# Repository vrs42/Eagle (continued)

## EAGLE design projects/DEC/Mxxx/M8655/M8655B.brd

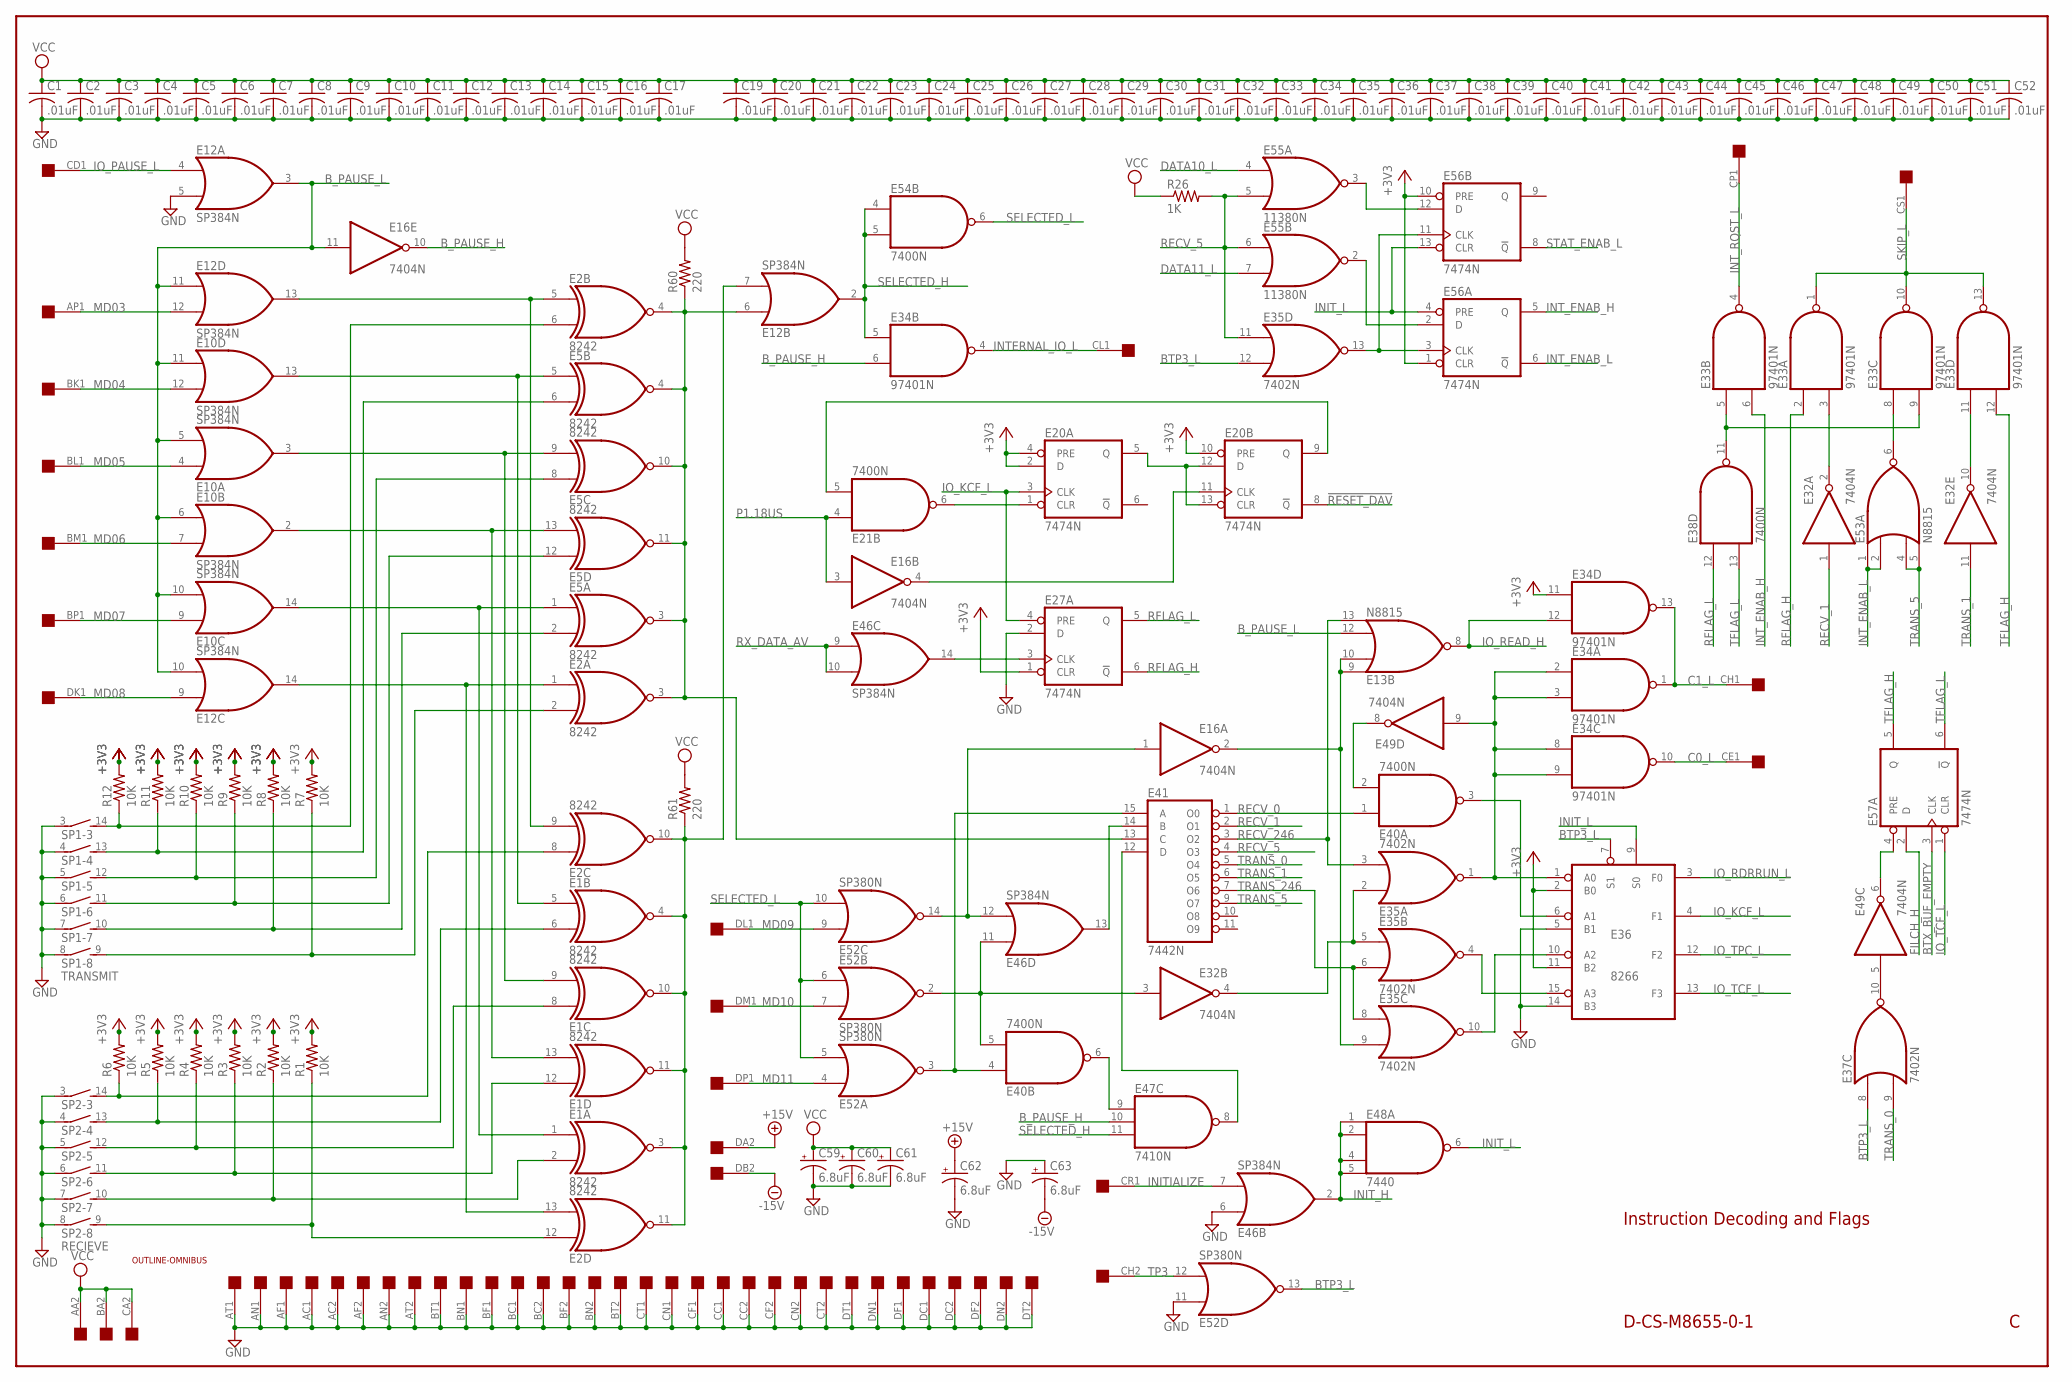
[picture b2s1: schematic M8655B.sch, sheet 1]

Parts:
C1, C2, C3, C4, C5, C6, C7, C8, C9, C10, C11, C12, C13, C14, C15, C16, C17, C19, C20, C21, C22, C23, C24, C25, C26, C27, C28, C29, C30, C31, C32, C33, C34, C35, C36, C37, C38, C39, C40, C41, C42, C43, C44, C45, C46, C47, C48, C49, C50, C51, C52: .01uF; C050-025X075
C59, C60, C61, C62, C63: 6.8uF; E12-8
E1, E2, E5: 8242; DIL14
E10, E12, E46: SP384N; DIL14
E13, E53: N8815; DIL14
E16, E32, E49: 7404N; DIL14
E20, E27, E56, E57: 7474N; DIL14
E21, E38, E40, E54: 7400N; DIL14
E33, E34: 97401N; DIL14
E35, E37: 7402N; DIL14
E36: 8266; DIL16
E41: 7442N; DIL16
E47: 7410N; DIL14
E48: 7440; DIL14
E52: SP380N; DIL14
E55: 11380N; DIL14
R1, R2, R3, R4, R5, R6, R7, R8, R9, R10, R11, R12: 10K; 0207/10
R26: 1K; 0207/10
R60, R61: 220; 0207/10
SP1: TRANSMIT; DIP08S
SP2: RECIEVE; DIP08S
U$1: OUTLINE-OMNIBUS; OMNIBUS
U$2: QUAD; EDGE-CON8

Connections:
!RESET_DAV: E20.8 (!Q); also elsewhere on the board
+3V3: E20.2 (D), E20.4 (PRE), E20.10 (PRE), E27.1 (CLR), E34.11 (I0), E36.2 (B0), E36.11 (B2), E56.1 (CLR), E56.10 (PRE), R1.2, R2.2, R3.2, R4.2, R5.2, R6.2, R7.2, R8.2, R9.2, R10.2, R11.2, R12.2; also elsewhere on the board
+15V: C62.+, U$2.DA2; also elsewhere on the board
-15V: C63.-, U$2.DB2; also elsewhere on the board
BTP3_L: E35.12 (I1), E36.7 (S1), E37.8 (I0), E52.13 (O)
BTX_BUF_EMPTY: E57.3 (CLK); also elsewhere on the board
B_PAUSE_H: E16.10 (O), E34.6 (I1), E47.10 (I1)
B_PAUSE_L: E10.5 (I1), E10.6 (I0), E10.10 (I1), E10.11 (I0), E12.3 (O), E12.10 (I1), E12.11 (I0), E13.12 (I2), E16.11 (I); also elsewhere on the board
C0_L: E34.10 (O), U$2.CE1
C1_L: E34.1 (O), E34.13 (O), U$2.CH1
DATA10_L: E55.4 (I0); also elsewhere on the board
DATA11_L: E55.7 (I1); also elsewhere on the board
FILCH_H: E57.2 (D); also elsewhere on the board
GND: C1.2, C2.2, C3.2, C4.2, C5.2, C6.2, C7.2, C8.2, C9.2, C10.2, C11.2, C12.2, C13.2, C14.2, C15.2, C16.2, C17.2, C19.2, C20.2, C21.2, C22.2, C23.2, C24.2, C25.2, C26.2, C27.2, C28.2, C29.2, C30.2, C31.2, C32.2, C33.2, C34.2, C35.2, C36.2, C37.2, C38.2, C39.2, C40.2, C41.2, C42.2, C43.2, C44.2, C45.2, C46.2, C47.2, C48.2, C49.2, C50.2, C51.2, C52.2, C59.-, C60.-, C61.-, C62.-, C63.+, E1.7 (GND), E2.7 (GND), E5.7 (GND), E10.1 (GND), E12.1 (GND), E12.5 (I1), E13.7 (GND), E16.7 (GND), E20.7 (GND), E21.7 (GND), E27.2 (D), E27.7 (GND), E32.7 (GND), E33.7 (GND), E34.7 (GND), E35.7 (GND), E36.5 (B1), E36.8 (GND), E36.14 (B3), E37.7 (GND), E38.7 (GND), E40.7 (GND), E41.8 (GND), E46.1 (GND), E46.6 (I0), E47.7 (GND), E48.7 (GND), E49.7 (GND), E52.1 (GND), E52.11 (I0), E53.7 (GND), E54.7 (GND), E55.1 (GND), E56.7 (GND), E57.7 (GND), SP1.3 (1), SP1.4 (1), SP1.5 (1), SP1.6 (1), SP1.7 (1), SP1.8 (1), SP2.3 (1), SP2.4 (1), SP2.5 (1), SP2.6 (1), SP2.7 (1), SP2.8 (1), U$2.AC1, U$2.AC2, U$2.AF1, U$2.AF2, U$2.AN1, U$2.AN2, U$2.AT1, U$2.AT2, U$2.BC1, U$2.BC2, U$2.BF1, U$2.BF2, U$2.BN1, U$2.BN2, U$2.BT1, U$2.BT2, U$2.CC1, U$2.CC2, U$2.CF1, U$2.CF2, U$2.CN1, U$2.CN2, U$2.CT1, U$2.CT2, U$2.DC1, U$2.DC2, U$2.DF1, U$2.DF2, U$2.DN1, U$2.DN2, U$2.DT1, U$2.DT2; also elsewhere on the board
INITIALIZE: E46.7 (I1), U$2.CR1
INIT_H: E46.2 (O), E48.1 (I0), E48.2 (I1), E48.4 (I2), E48.5 (I3); also elsewhere on the board
INIT_L: E36.9 (S0), E48.6 (O), E56.4 (PRE), E56.13 (CLR); also elsewhere on the board
INTERNAL_IO_L: E34.4 (O), U$2.CL1
INT_ENAB_H: E33.6 (I1), E56.5 (Q)
INT_ENAB_L: E53.1 (I0), E53.2 (I1), E56.6 (!Q)
INT_RQST_L: E33.4 (O), U$2.CP1
IO_KCF_L: E20.3 (CLK), E27.4 (PRE), E36.4 (F1)
IO_PAUSE_L: E12.4 (I0), U$2.CD1
IO_RDRRUN_L: E36.3 (F0); also elsewhere on the board
IO_READ_H: E13.8 (O), E34.12 (I1); also elsewhere on the board
IO_TCF_L: E36.13 (F3), E57.1 (CLR)
IO_TPC_L: E36.12 (F2); also elsewhere on the board
MD03: E12.12 (I1), U$2.AP1
MD04: E10.12 (I1), U$2.BK1
MD05: E10.4 (I0), U$2.BL1
MD06: E10.7 (I1), U$2.BM1
MD07: E10.9 (I0), U$2.BP1
MD08: E12.9 (I0), U$2.DK1
MD09: E52.9 (I0), U$2.DL1
MD10: E52.7 (I1), U$2.DM1
MD11: E52.4 (I0), U$2.DP1
unnamed: E2.6 (I1), R12.1, SP1.14 (2)
unnamed: E5.6 (I1), R11.1, SP1.13 (2)
unnamed: E5.8 (I0), R10.1, SP1.12 (2)
unnamed: E5.12 (I0), R9.1, SP1.11 (2)
unnamed: E5.2 (I1), R8.1, SP1.10 (2)
unnamed: E2.2 (I1), R7.1, SP1.9 (2)
unnamed: E2.5 (I0), E2.9 (I1), E12.13 (O)
unnamed: E2.8 (I0), R6.1, SP2.14 (2)
unnamed: E1.6 (I1), R5.1, SP2.13 (2)
unnamed: E1.8 (I0), R4.1, SP2.12 (2)
unnamed: E1.12 (I0), R3.1, SP2.11 (2)
unnamed: E1.2 (I1), R2.1, SP2.10 (2)
unnamed: E2.12 (I0), R1.1, SP2.9 (2)
unnamed: E1.5 (I0), E5.5 (I0), E10.13 (O)
unnamed: E1.9 (I1), E5.9 (I1), E10.3 (O)
unnamed: E1.13 (I1), E5.13 (I1), E10.2 (O)
unnamed: E1.1 (I0), E5.1 (I0), E10.14 (O)
unnamed: E2.1 (I0), E2.13 (I1), E12.14 (O)
unnamed: E2.3 (O), E2.4 (O), E5.3 (O), E5.4 (O), E5.10 (O), E5.11 (O), E12.6 (I0), E41.13 (C), R60.1
unnamed: E1.3 (O), E1.4 (O), E1.10 (O), E1.11 (O), E2.10 (O), E2.11 (O), E12.7 (I1), R61.1
unnamed: E32.3 (I), E40.5 (I1), E46.11 (I0), E52.2 (O)
unnamed: E16.1 (I), E46.12 (I1), E52.14 (O)
unnamed: E40.4 (I0), E41.15 (A), E52.3 (O)
unnamed: E34.2 (I0), E34.3 (I1), E34.8 (I0), E34.9 (I1), E35.1 (O), E36.1 (A0), E49.9 (I)
unnamed: E41.14 (B), E46.13 (O)
unnamed: E40.6 (O), E47.9 (I0)
unnamed: E32.4 (O), E35.2 (I0), E35.5 (I0)
unnamed: E41.12 (D), E47.8 (O)
unnamed: E13.9 (I0), E13.10 (I1), E16.2 (O), E35.9 (I1)
unnamed: E40.2 (I1), E49.8 (O)
unnamed: E35.4 (O), E36.15 (A3)
unnamed: E35.10 (O), E36.10 (A2)
unnamed: E36.6 (A1), E40.3 (O)
unnamed: E20.5 (Q), E20.12 (D), E20.13 (CLR)
unnamed: E20.1 (CLR), E21.6 (O)
unnamed: E27.3 (CLK), E46.14 (O)
unnamed: E16.4 (O), E20.11 (CLK)
unnamed: E20.9 (Q), E21.5 (I1)
unnamed: E35.13 (O), E56.3 (CLK), E56.11 (CLK)
unnamed: E55.2 (O), E56.2 (D)
unnamed: E55.3 (O), E56.12 (D)
unnamed: E37.10 (O), E49.5 (I)
unnamed: E49.6 (O), E57.4 (PRE)
unnamed: E32.2 (O), E33.3 (I1)
unnamed: E32.10 (O), E33.11 (I0)
unnamed: E33.8 (I0), E53.6 (O)
unnamed: E33.5 (I0), E33.9 (I1), E38.11 (O)
P1.18US: E16.3 (I), E21.4 (I0); also elsewhere on the board
RECV_0: E40.1 (I0), E41.1 (O0)
RECV_1: E32.1 (I), E41.2 (O1)
RECV_5: E35.11 (I0), E41.4 (O3), E55.5 (I1), E55.6 (I0), R26.2
RECV_246: E13.13 (I3), E35.3 (I1), E41.3 (O2)
RFLAG_H: E27.6 (!Q), E33.2 (I0)
RFLAG_L: E27.5 (Q), E38.12 (I0)
RX_DATA_AV: E46.9 (I0), E46.10 (I1); also elsewhere on the board
SELECTED_H: E12.2 (O), E34.5 (I0), E47.11 (I2), E54.4 (I0), E54.5 (I1)
SELECTED_L: E52.5 (I1), E52.6 (I0), E52.10 (I1), E54.6 (O)
SKIP_L: E33.1 (O), E33.10 (O), E33.13 (O), U$2.CS1
STAT_ENAB_L: E56.8 (!Q); also elsewhere on the board
TFLAG_H: E33.12 (I1), E57.5 (Q)
TFLAG_L: E38.13 (I1), E57.6 (!Q)
TP3: E52.12 (I1), U$2.CH2
TRANS_0: E37.9 (I1), E41.5 (O4)
TRANS_1: E32.11 (I), E41.6 (O5)
TRANS_5: E41.9 (O7), E53.4 (I2), E53.5 (I3)
TRANS_246: E35.6 (I1), E35.8 (I0), E41.7 (O6)
VCC: C1.1, C2.1, C3.1, C4.1, C5.1, C6.1, C7.1, C8.1, C9.1, C10.1, C11.1, C12.1, C13.1, C14.1, C15.1, C16.1, C17.1, C19.1, C20.1, C21.1, C22.1, C23.1, C24.1, C25.1, C26.1, C27.1, C28.1, C29.1, C30.1, C31.1, C32.1, C33.1, C34.1, C35.1, C36.1, C37.1, C38.1, C39.1, C40.1, C41.1, C42.1, C43.1, C44.1, C45.1, C46.1, C47.1, C48.1, C49.1, C50.1, C51.1, C52.1, C59.+, C60.+, C61.+, E1.14 (VCC), E2.14 (VCC), E5.14 (VCC), E10.8 (VCC), E12.8 (VCC), E13.14 (VCC), E16.14 (VCC), E20.14 (VCC), E21.14 (VCC), E27.14 (VCC), E32.14 (VCC), E33.14 (VCC), E34.14 (VCC), E35.14 (VCC), E36.16 (VCC), E37.14 (VCC), E38.14 (VCC), E40.14 (VCC), E41.16 (VCC), E46.8 (VCC), E47.14 (VCC), E48.14 (VCC), E49.14 (VCC), E52.8 (VCC), E53.14 (VCC), E54.14 (VCC), E55.8 (VCC), E56.14 (VCC), E57.14 (VCC), R26.1, R60.2, R61.2, U$2.AA2, U$2.BA2, U$2.CA2; also elsewhere on the board

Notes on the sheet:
Instruction Decoding and Flags
D-CS-M8655-0-1

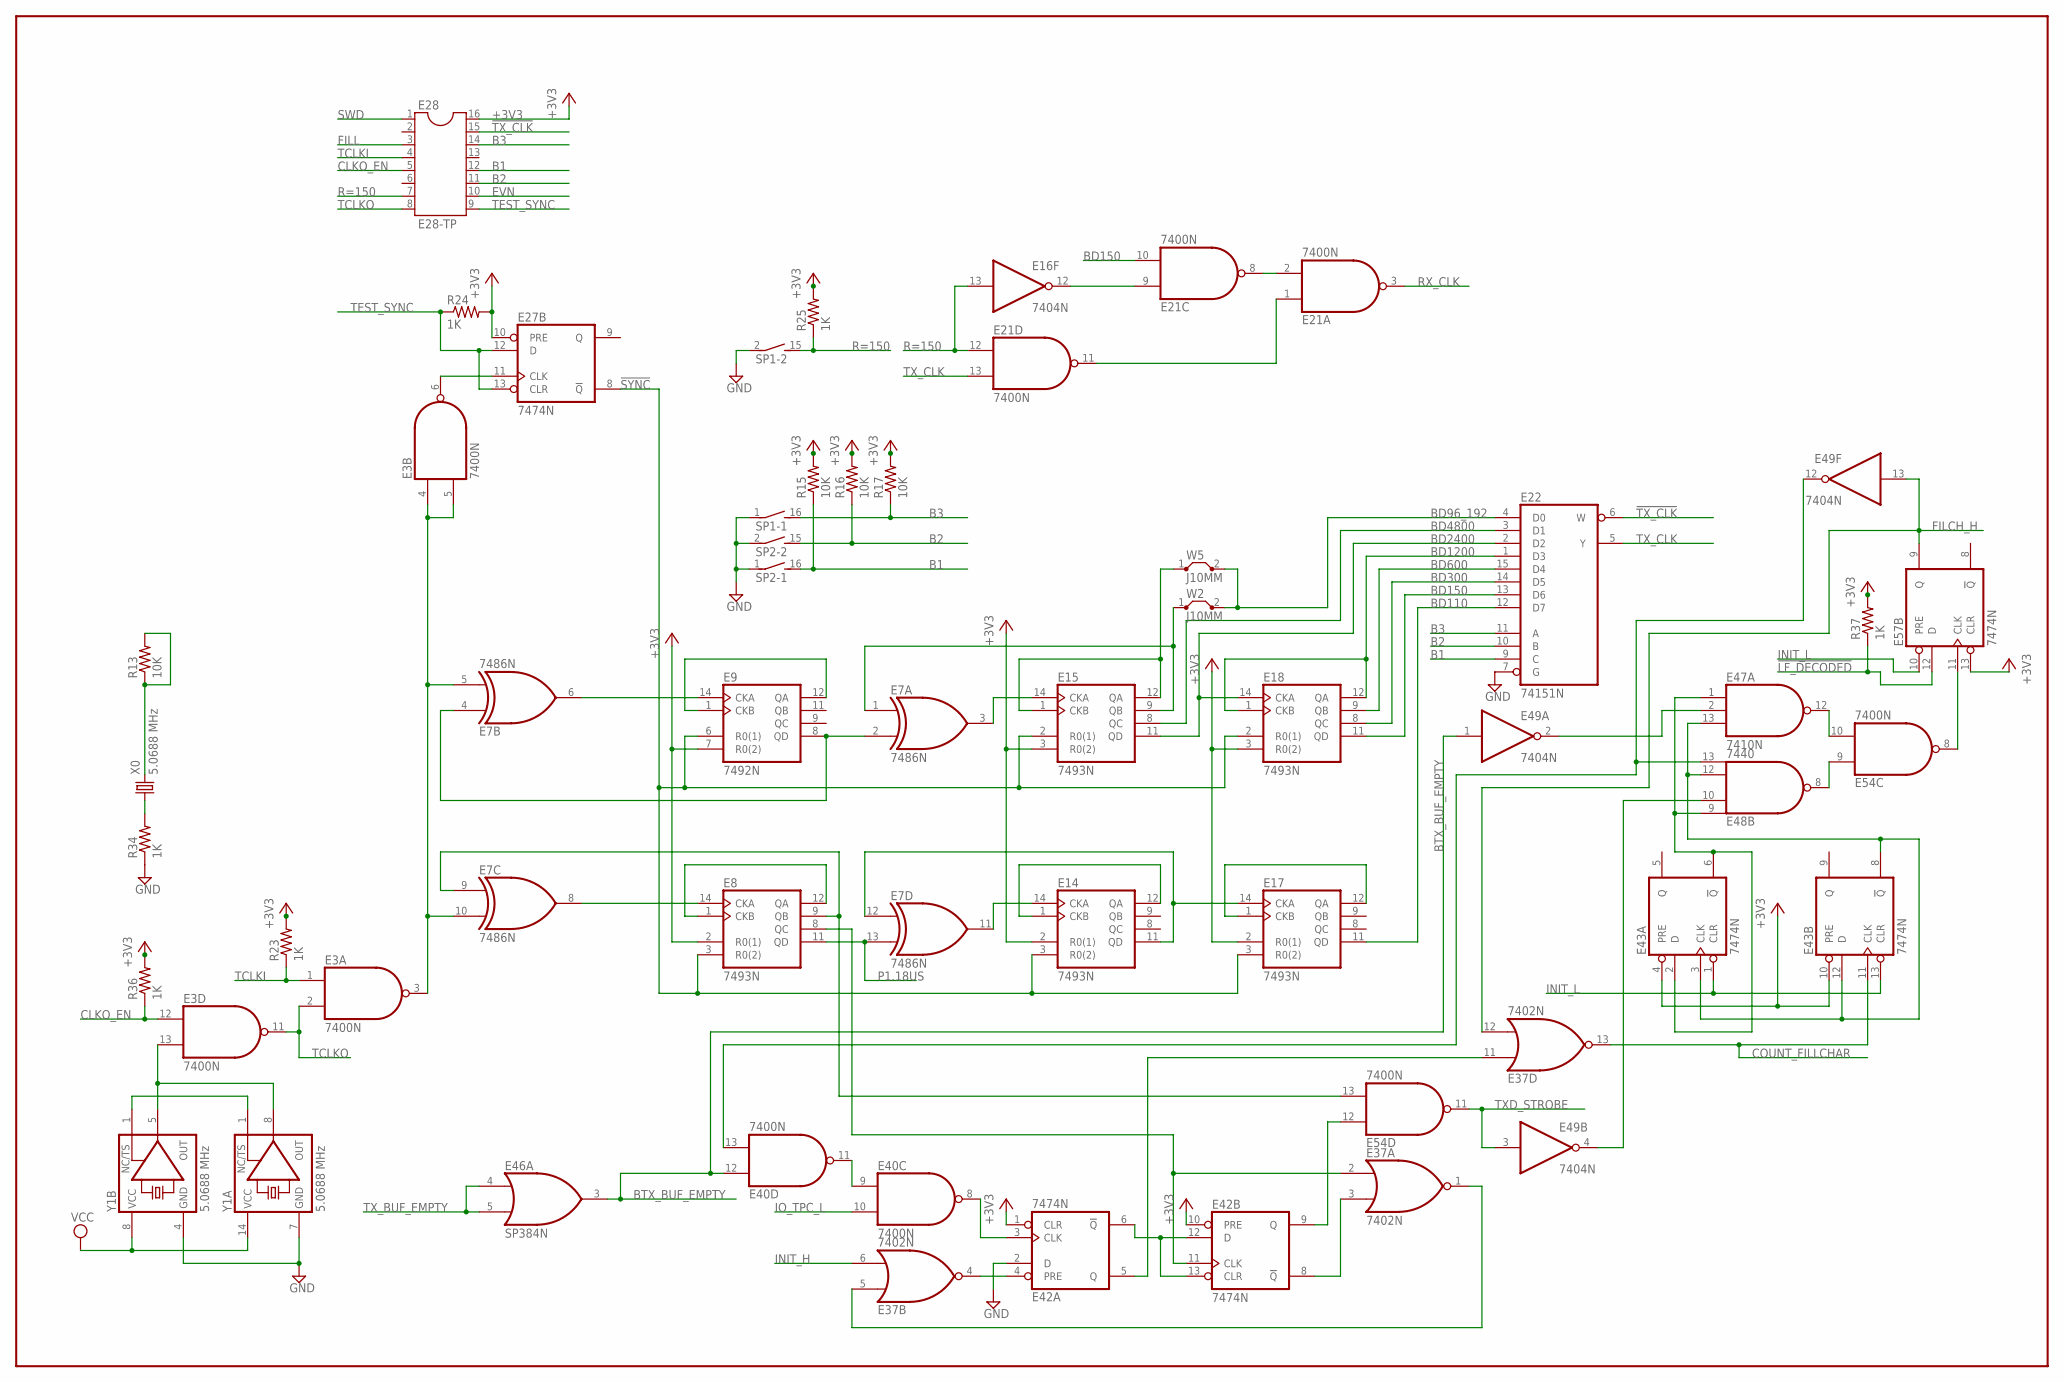
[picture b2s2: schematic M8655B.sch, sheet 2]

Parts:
E3, E21, E40, E54: 7400N; DIL14
E7: 7486N; DIL14
E8, E14, E15, E17, E18: 7493N; DIL14
E9: 7492N; DIL14
E16, E49: 7404N; DIL14
E22: 74151N; DIL16
E27, E42, E43, E57: 7474N; DIL14
E28: E28-TP; SOCKET-16
E37: 7402N; DIL14
E46: SP384N; DIL14
E47: 7410N; DIL14
E48: 7440; DIL14
R13, R15, R16, R17: 10K; 0207/10
R23, R24, R25, R34, R36, R37: 1K; 0207/10
SP1: TRANSMIT; DIP08S
SP2: RECIEVE; DIP08S
W2, W5: J10MM; 10
X0: 5.0688 MHz; HC33U-H
Y1A: 5.0688 MHz; DIL14S
Y1B: 5.0688 MHz; DIL08S

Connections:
!FILCH: E40.13 (I1), E48.13 (I3), E49.12 (O)
!LF_DECODED: E57.12 (D), R37.1; also elsewhere on the board
!SYNC: E8.3 (R0(2)), E9.6 (R0(1)), E14.3 (R0(2)), E15.2 (R0(1)), E17.3 (R0(2)), E18.2 (R0(1)), E27.8 (!Q)
!TX_CLK: E22.6 (W), E28.15
+3V3: E8.2 (R0(1)), E9.7 (R0(2)), E14.2 (R0(1)), E15.3 (R0(2)), E17.2 (R0(1)), E18.3 (R0(2)), E27.10 (PRE), E28.16, E42.1 (CLR), E42.10 (PRE), E43.4 (PRE), E43.10 (PRE), E57.13 (CLR), R15.2, R16.2, R17.2, R23.2, R24.2, R25.2, R36.2, R37.2; also elsewhere on the board
B1: E22.9 (C), E28.12, R15.1, SP2.16 (2)
B2: E22.10 (B), E28.11, R16.1, SP2.15 (2)
B3: E22.11 (A), E28.14, R17.1, SP1.16 (2)
BD96_192: E22.4 (D0), W2.2, W5.2
BD110: E17.11 (QD), E22.12 (D7)
BD150: E18.11 (QD), E21.10 (I1), E22.13 (D6)
BD300: E18.8 (QC), E22.14 (D5)
BD600: E18.9 (QB), E22.15 (D4)
BD1200: E18.1 (CKB), E18.12 (QA), E22.1 (D3)
BD2400: E15.11 (QD), E18.14 (CKA), E22.2 (D2)
BD4800: E15.8 (QC), E22.3 (D1)
BTX_BUF_EMPTY: E40.12 (I0), E46.3 (O), E49.1 (I); also elsewhere on the board
CLKO_EN: E3.12 (I0), E28.5, R36.1
COUNT_FILLCHAR: E37.13 (O), E43.11 (CLK); also elsewhere on the board
EVN: E28.10; also elsewhere on the board
FILCH_H: E37.12 (I1), E49.13 (I), E57.9 (Q); also elsewhere on the board
FILL: E28.3; also elsewhere on the board
GND: E3.7 (GND), E7.7 (GND), E8.10 (GND), E9.10 (GND), E14.10 (GND), E15.10 (GND), E16.7 (GND), E17.10 (GND), E18.10 (GND), E21.7 (GND), E22.7 (G), E22.8 (GND), E27.7 (GND), E37.7 (GND), E40.7 (GND), E42.2 (D), E42.7 (GND), E43.7 (GND), E46.1 (GND), E47.7 (GND), E48.7 (GND), E49.7 (GND), E54.7 (GND), E57.7 (GND), R34.1, SP1.1, SP1.2 (1), SP2.1, SP2.2 (1), Y1A.7 (GND), Y1B.4 (GND); also elsewhere on the board
INIT_H: E37.6 (I1); also elsewhere on the board
INIT_L: E43.1 (CLR), E43.13 (CLR), E57.10 (PRE); also elsewhere on the board
IO_TPC_L: E40.10 (I1); also elsewhere on the board
unnamed: E3.6 (O), E27.11 (CLK)
unnamed: E3.3 (O), E3.4 (I0), E3.5 (I1), E7.5 (I1), E7.10 (I1)
unnamed: E3.13 (I1), Y1A.8 (OUT), Y1B.5 (OUT)
unnamed: Y1A.1 (TS), Y1B.1 (TS)
unnamed: E8.1 (CKB), E8.12 (QA)
unnamed: E7.9 (I0), E8.9 (QB), E54.13 (I1)
unnamed: E7.8 (O), E8.14 (CKA)
unnamed: E7.6 (O), E9.14 (CKA)
unnamed: E9.1 (CKB), E9.12 (QA)
unnamed: E7.2 (I1), E7.4 (I0), E9.8 (QD)
unnamed: E7.3 (O), E15.14 (CKA)
unnamed: E15.1 (CKB), E15.12 (QA), W5.1
unnamed: E7.1 (I0), E15.9 (QB), W2.1
unnamed: E16.12 (O), E21.9 (I0)
unnamed: E21.2 (I1), E21.8 (O)
unnamed: E21.1 (I0), E21.11 (O)
unnamed: E7.11 (O), E14.14 (CKA)
unnamed: E14.1 (CKB), E14.12 (QA)
unnamed: E7.12 (I0), E14.11 (QD), E17.14 (CKA)
unnamed: E17.1 (CKB), E17.12 (QA)
unnamed: E40.9 (I0), E40.11 (O)
unnamed: E37.1 (O), E37.5 (I0)
unnamed: E37.4 (O), E42.4 (PRE)
unnamed: E8.8 (QC), E37.2 (I0), E42.11 (CLK)
unnamed: E40.8 (O), E42.3 (CLK)
unnamed: E42.6 (!Q), E42.12 (D), E42.13 (CLR)
unnamed: E37.11 (I0), E42.5 (Q)
unnamed: E43.2 (D), E43.6 (!Q), E47.1 (I0), E48.9 (I0)
unnamed: E42.9 (Q), E54.12 (I0)
unnamed: E37.3 (I1), E42.8 (!Q)
unnamed: E43.3 (CLK), E43.8 (!Q), E43.12 (D), E47.13 (I2), E48.12 (I2)
unnamed: E47.2 (I1), E49.2 (O)
unnamed: E48.10 (I1), E49.4 (O)
unnamed: E47.12 (O), E54.10 (I1)
unnamed: E48.8 (O), E54.9 (I0)
unnamed: E54.8 (O), E57.11 (CLK)
unnamed: R34.2, X0.1
unnamed: R13.1, R13.2, X0.2
P1.18US: E7.13 (I1), E8.11 (QD); also elsewhere on the board
R=150: E16.13 (I), E21.12 (I0), E28.7, R25.1, SP1.15 (2)
RX_CLK: E21.3 (O); also elsewhere on the board
SWD: E28.1; also elsewhere on the board
TCLKI: E3.1 (I0), E28.4, R23.1
TCLKO: E3.2 (I1), E3.11 (O), E28.8
TEST_SYNC: E27.12 (D), E27.13 (CLR), E28.9, R24.1
TXD_STROBE: E49.3 (I), E54.11 (O); also elsewhere on the board
TX_BUF_EMPTY: E46.4 (I0), E46.5 (I1); also elsewhere on the board
TX_CLK: E21.13 (I1), E22.5 (Y); also elsewhere on the board
VCC: E3.14 (VCC), E7.14 (VCC), E8.5 (VCC), E9.5 (VCC), E14.5 (VCC), E15.5 (VCC), E16.14 (VCC), E17.5 (VCC), E18.5 (VCC), E21.14 (VCC), E22.16 (VCC), E27.14 (VCC), E37.14 (VCC), E40.14 (VCC), E42.14 (VCC), E43.14 (VCC), E46.8 (VCC), E47.14 (VCC), E48.14 (VCC), E49.14 (VCC), E54.14 (VCC), E57.14 (VCC), Y1A.14 (VCC), Y1B.8 (VCC); also elsewhere on the board

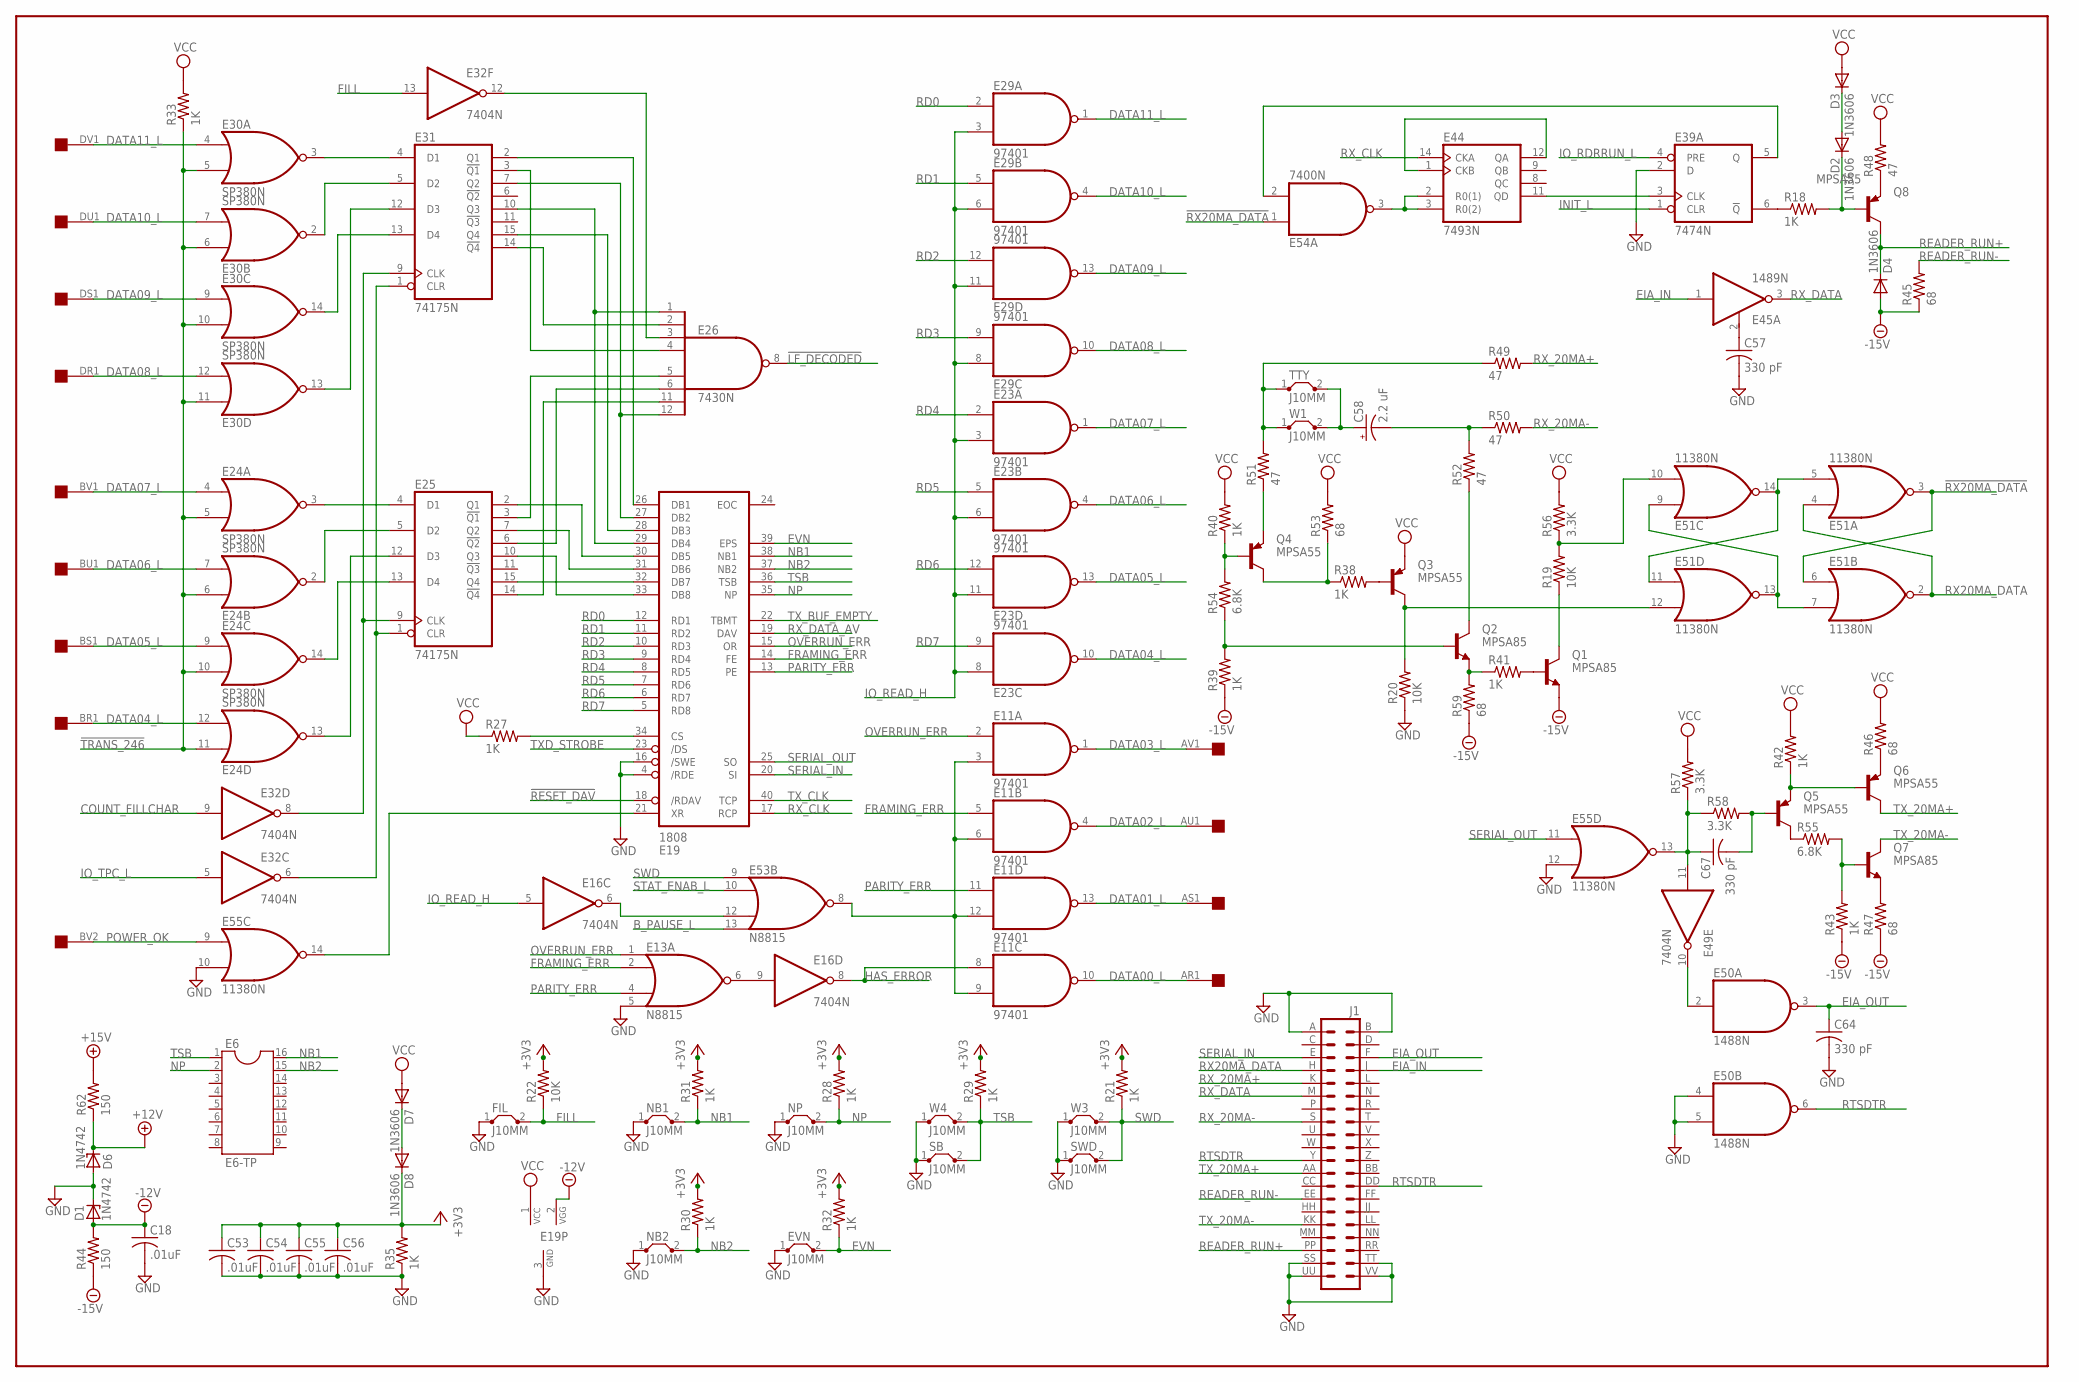
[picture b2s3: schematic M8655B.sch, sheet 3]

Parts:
C18, C53, C54, C55, C56: .01uF; C050-025X075
C57, C64, C67: 330 pF; C050-025X075
C58: 2.2 uF; E12-8
D1, D6: 1N4742; DO41Z10
D2, D3, D4, D7, D8: 1N3606; DO35-10
E6: E6-TP; SOCKET-16
E11, E23, E29: 97401; DIL14
E13, E53: N8815; DIL14
E16, E32, E49: 7404N; DIL14
E19: 1808; DIL40
E24, E30: SP380N; DIL14
E25, E31: 74175N; DIL16
E26: 7430N; DIL14
E39: 7474N; DIL14
E44: 7493N; DIL14
E45: 1489N; DIL14
E50: 1488N; DIL14
E51, E55: 11380N; DIL14
E54: 7400N; DIL14
EVN: J10MM; 10
FIL: J10MM; 10
J1: DEC40PINH
NB1, NB2: J10MM; 10
NP: J10MM; 10
Q1, Q2, Q7: MPSA85; TO5
Q3, Q4, Q5, Q6, Q8: MPSA55; TO5
R18, R21, R27, R28, R29, R30, R31, R32, R33, R35, R38, R39, R40, R41, R42, R43: 1K; 0207/10
R19, R20, R22: 10K; 0207/10
R44, R62: 150; 0207/10
R45, R46, R47, R53, R59: 68; 0207/10
R48, R49, R50, R51, R52: 47; 0207/10
R54, R55: 6.8K; 0207/10
R56, R57, R58: 3.3K; 0207/10
SB: J10MM; 10
SWD: J10MM; 10
TTY: J10MM; 10
U$2: QUAD; EDGE-CON8
W1, W3, W4: J10MM; 10

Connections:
!LF_DECODED: E26.8 (O); also elsewhere on the board
!RESET_DAV: E19.18 (/RDAV); also elsewhere on the board
!RX20MA_DATA: E51.3 (O), E51.6 (I0), E54.1 (I0)
!TRANS_246: E24.5 (I1), E24.6 (I0), E24.10 (I1), E24.11 (I0), E30.5 (I1), E30.6 (I0), E30.10 (I1), E30.11 (I0), R33.1
+3V3: C53.1, C54.1, C55.1, C56.1, D8.C, R21.2, R22.2, R28.2, R29.2, R30.2, R31.2, R32.2, R35.2; also elsewhere on the board
+12V: D6.C, E50.14 (+12V), R62.1
+15V: R62.2; also elsewhere on the board
-12V: C18.1, D1.A, E19.2 (VGG), E50.1 (-12V), R44.2
-15V: D4.A, Q1.1 (E), R39.1, R43.1, R44.1, R45.1, R47.1, R59.1; also elsewhere on the board
B_PAUSE_L: E53.13 (I3); also elsewhere on the board
COUNT_FILLCHAR: E32.9 (I); also elsewhere on the board
DATA00_L: E11.10 (O), U$2.AR1
DATA01_L: E11.13 (O), U$2.AS1
DATA02_L: E11.4 (O), U$2.AU1
DATA03_L: E11.1 (O), U$2.AV1
DATA04_L: E23.10 (O), E24.12 (I1), U$2.BR1
DATA05_L: E23.13 (O), E24.9 (I0), U$2.BS1
DATA06_L: E23.4 (O), E24.7 (I1), U$2.BU1
DATA07_L: E23.1 (O), E24.4 (I0), U$2.BV1
DATA08_L: E29.10 (O), E30.12 (I1), U$2.DR1
DATA09_L: E29.13 (O), E30.9 (I0), U$2.DS1
DATA10_L: E29.4 (O), E30.7 (I1), U$2.DU1; also elsewhere on the board
DATA11_L: E29.1 (O), E30.4 (I0), U$2.DV1; also elsewhere on the board
EIA_IN: E45.1 (I), J1.J (8)
EIA_OUT: C64.1, E50.3 (O), J1.F (6)
EVN: E19.39 (EPS), EVN.2, R32.1; also elsewhere on the board
FILL: E32.13 (I), FIL.2, R22.1; also elsewhere on the board
FRAMING_ERR: E11.5 (I0), E13.2 (I1), E19.14 (FE)
GND: C18.2, C53.2, C54.2, C55.2, C56.2, C57.2, C64.2, D1.C, D6.A, E11.7 (GND), E13.5 (I3), E13.7 (GND), E16.7 (GND), E19.3 (GND), E19.4 (/RDE), E19.16 (/SWE), E23.7 (GND), E24.1 (GND), E25.8 (GND), E26.7 (GND), E29.7 (GND), E30.1 (GND), E31.8 (GND), E32.7 (GND), E39.2 (D), E39.7 (GND), E44.10 (GND), E45.7 (GND), E49.7 (GND), E50.4 (I0), E50.5 (I1), E50.7 (GND), E51.1 (GND), E53.7 (GND), E54.7 (GND), E55.1 (GND), E55.10 (I1), E55.12 (I1), EVN.1, FIL.1, J1.A (1), J1.B (2), J1.SS (37), J1.TT (38), J1.UU (39), J1.VV (40), NB1.1, NB2.1, NP.1, R20.1, R35.1, SB.1, SWD.1, W3.1, W4.1; also elsewhere on the board
HAS_ERROR: E11.8 (I0), E16.8 (O)
INIT_L: E39.1 (CLR); also elsewhere on the board
IO_RDRRUN_L: E39.4 (PRE); also elsewhere on the board
IO_READ_H: E16.5 (I), E23.3 (I1), E23.6 (I1), E23.8 (I0), E23.11 (I0), E29.3 (I1), E29.6 (I1), E29.8 (I0), E29.11 (I0); also elsewhere on the board
IO_TPC_L: E32.5 (I); also elsewhere on the board
unnamed: E30.3 (O), E31.4 (D1)
unnamed: E30.2 (O), E31.5 (D2)
unnamed: E30.14 (O), E31.13 (D4)
unnamed: E30.13 (O), E31.12 (D3)
unnamed: E19.26 (DB1), E31.2 (Q1)
unnamed: E24.3 (O), E25.4 (D1)
unnamed: E24.2 (O), E25.5 (D2)
unnamed: E24.14 (O), E25.13 (D4)
unnamed: E24.13 (O), E25.12 (D3)
unnamed: E25.9 (CLK), E31.9 (CLK), E32.8 (O)
unnamed: E25.1 (CLR), E31.1 (CLR), E32.6 (O)
unnamed: E19.27 (DB2), E26.12 (I7), E31.7 (Q2)
unnamed: E19.28 (DB3), E31.15 (Q4)
unnamed: E19.29 (DB4), E26.1 (I0), E31.10 (Q3)
unnamed: E19.30 (DB5), E25.2 (Q1)
unnamed: E19.31 (DB6), E25.7 (Q2)
unnamed: E19.33 (DB8), E25.10 (Q3)
unnamed: E19.32 (DB7), E25.15 (Q4)
unnamed: E26.4 (I3), E31.3 (!Q1)
unnamed: E26.2 (I1), E31.14 (!Q4)
unnamed: E26.3 (I2), E32.12 (O)
unnamed: E25.3 (!Q1), E26.5 (I4)
unnamed: E25.6 (!Q2), E26.6 (I5)
unnamed: E25.14 (!Q4), E26.11 (I6)
unnamed: E11.3 (I1), E11.6 (I1), E11.9 (I1), E11.12 (I1), E53.8 (O)
unnamed: E13.6 (O), E16.9 (I)
unnamed: E19.34 (CS), R27.2
unnamed: E44.2 (R0(1)), E44.3 (R0(2)), E54.3 (O)
unnamed: E44.1 (CKB), E44.12 (QA)
unnamed: E16.6 (O), E53.12 (I2)
unnamed: E39.3 (CLK), E44.11 (QD)
unnamed: E39.5 (Q), E54.2 (I1)
unnamed: E39.6 (!Q), R18.1
unnamed: D2.C, Q8.2 (B), R18.2
unnamed: Q8.1 (E), R48.1
unnamed: D2.A, D3.C
unnamed: C57.1, E45.2 (RC)
unnamed: C58.-, R50.1, R52.2
unnamed: C58.+, TTY.2, W1.2
unnamed: R49.1, R51.2, TTY.1, W1.1
unnamed: E49.10 (O), E50.2 (I)
unnamed: Q6.1 (E), R46.1
unnamed: Q7.1 (E), R47.2
unnamed: Q5.1 (E), Q6.2 (B), R42.1
unnamed: Q5.3 (C), R55.1
unnamed: Q7.2 (B), R43.2, R55.2
unnamed: C67.2, Q5.2 (B), R58.2
unnamed: C67.1, E49.11 (I), E55.13 (O), R57.1, R58.1
unnamed: Q2.2 (B), R39.2, R54.1
unnamed: Q4.2 (B), R40.1, R54.2
unnamed: Q4.3 (C), R38.1, R53.1
unnamed: Q4.1 (E), R51.1
unnamed: Q3.2 (B), R38.2
unnamed: E51.12 (I1), Q3.3 (C), R20.2
unnamed: Q2.3 (C), R52.1
unnamed: Q2.1 (E), R41.1, R59.2
unnamed: Q1.2 (B), R41.2
unnamed: Q1.3 (C), R19.1
unnamed: E51.10 (I1), R19.2, R56.1
unnamed: E51.7 (I1), E51.9 (I0), E51.13 (O)
unnamed: E51.5 (I1), E51.11 (I0), E51.14 (O)
unnamed: D7.C, D8.A
NB1: E6.16, E19.38 (NB1), NB1.2, R31.1
NB2: E6.15, E19.37 (NB2), NB2.2, R30.1
NP: E6.2, E19.35 (NP), NP.2, R28.1
OVERRUN_ERR: E11.2 (I0), E13.1 (I0), E19.15 (OR)
PARITY_ERR: E11.11 (I0), E13.4 (I2), E19.13 (PE)
POWER_OK: E55.9 (I0), U$2.BV2
RD0: E19.12 (RD1), E29.2 (I0)
RD1: E19.11 (RD2), E29.5 (I0)
RD2: E19.10 (RD3), E29.12 (I1)
RD3: E19.9 (RD4), E29.9 (I1)
RD4: E19.8 (RD5), E23.2 (I0)
RD5: E19.7 (RD6), E23.5 (I0)
RD6: E19.6 (RD7), E23.12 (I1)
RD7: E19.5 (RD8), E23.9 (I1)
READER_RUN+: D4.C, J1.PP (35), Q8.3 (C)
READER_RUN-: J1.EE (27), R45.2
RTSDTR: E50.6 (O), J1.DD (26), J1.Y (21)
RX20MA_DATA: E51.2 (O), E51.4 (I0), J1.H (7)
RX_20MA+: J1.K (9), R49.2
RX_20MA-: J1.S (15), R50.2
RX_CLK: E19.17 (RCP), E44.14 (CKA); also elsewhere on the board
RX_DATA: E45.3 (O), J1.M (11)
RX_DATA_AV: E19.19 (DAV); also elsewhere on the board
SERIAL_IN: E19.20 (SI), J1.E (5)
SERIAL_OUT: E19.25 (SO), E55.11 (I0)
STAT_ENAB_L: E53.10 (I1); also elsewhere on the board
SWD: E53.9 (I0), R21.1, SWD.2, W3.2; also elsewhere on the board
TSB: E6.1, E19.36 (TSB), R29.1, SB.2, W4.2
TXD_STROBE: E19.23 (/DS); also elsewhere on the board
TX_20MA+: J1.AA (23), Q6.3 (C)
TX_20MA-: J1.KK (31), Q7.3 (C)
TX_BUF_EMPTY: E19.22 (TBMT); also elsewhere on the board
TX_CLK: E19.40 (TCP); also elsewhere on the board
VCC: D3.A, D7.A, E11.14 (VCC), E13.14 (VCC), E16.14 (VCC), E19.1 (VCC), E23.14 (VCC), E24.8 (VCC), E25.16 (VCC), E26.14 (VCC), E29.14 (VCC), E30.8 (VCC), E31.16 (VCC), E32.14 (VCC), E39.14 (VCC), E44.5 (VCC), E45.14 (VCC), E49.14 (VCC), E51.8 (VCC), E53.14 (VCC), E54.14 (VCC), E55.8 (VCC), Q3.1 (E), R27.1, R33.2, R40.2, R42.2, R46.2, R48.2, R53.2, R56.2, R57.2; also elsewhere on the board
XR: E19.21 (XR), E55.14 (O)

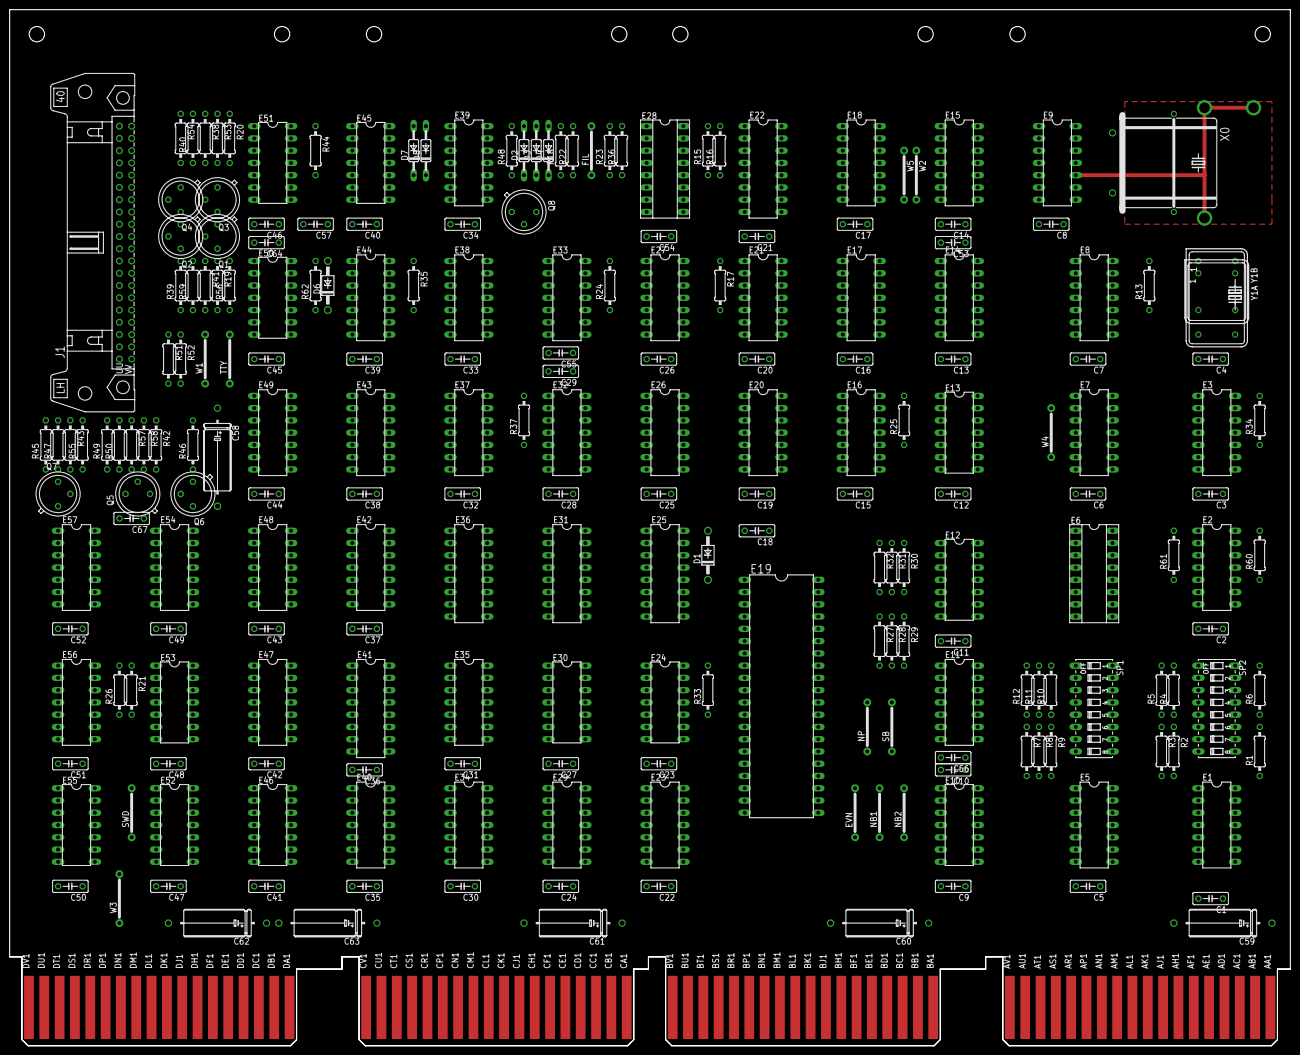
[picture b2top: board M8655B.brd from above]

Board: 2 copper layers, 265.3 x 214.6 mm, 218 parts (0 on the bottom side), 276 nets.
